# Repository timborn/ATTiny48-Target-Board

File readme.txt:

Fri Jun 16 17:11:15 MST 2023
----------------------------
_X_ add pads for ISP connector
_X_ gotta have an LED to we can detect life
_X_ decoupling caps between VCC and GND
_na pull-up resistor on VCC
    Data sheet section 22, Electrical Characteristics shows the reset pin
    has a built-in pull-up resistor of between 30 and 60 Ohms, so we shouldn't 
    need an external pull-up, especially for a bare bones system.
_X_ noise filtering ckt between VCC and AVCC (so ADC works better)
_X_ pin headers to fit std breadboard
_X_ reset button
_X_ panelize boards
_X_ fix installation of kikit that broke with upgrade of KiCad to 7.0.5
___ UNpanelize board

1.  Git Tag each version and make sure you push tags to origin
    https://git-scm.com/book/en/v2/Git-Basics-Tagging
2.  When I went to PCBWAY to place the order, I had panelized 2x4 which ended up
    being 110.5 x 104.7mm.  The price for the boards was $35.  
    When I dropped the size to fit inside 100x100mm the price dropped to $5.
3.  When generating the Gerber files I got a stern warning:
    "Global solder mask minimum width and/or margin are not set to 0.
    Most board manufacturers expect 0 and use their own constraints for
    solder mask minimum width."

    File / Board Setup / Board Stackup / Solder Mask/Paste
    set 'Solder mask expansion' to 0
    set 'Solder mask minimum web width' to 0

    I compared my settings to the requirements from PCBWAY:
    https://www.pcbway.com/pcb_prototype/Pinted_Circuit_Board_Prototype.html
    I didn't find anything about solder mask web width, so I set it at zero
    per KiCad recommendation.  I did change minimum clearance between traces
    to 3mil (0.076mm) per PCBWAY recommendation.  These changes went in post v1.0.

4.  Found a forked trace on pin 22 GND.  Cleaned that up.
5.  Having difficulty with paneling.  Crashes often, and rarely allows me to iterate
    without having to start over with a clean project.  I picked off the command
    line that it builds (uses kikit) but it throws some error when I run it from 
    the command line.  I think I could iterate faster over panels if I had
    the command line stuff working.
6.  ... to that end, I upgraded from KiCad 7.02 to 7.0.5.  I think kikit maybe brew.
    When I installed 7.0.5 over 7.0.2 it went through the motions, but silently failed.
    I had to move the old KiCad folder out of /Applications for installation to complete.
7.  After upgrading to KiCad 7.0.5 it complained about KiKit and sent me here to install it:
    https://github.com/yaqwsx/KiKit/blob/master/doc/installation.md

    Before:
    R2D2:ATTiny48-Target-Board timborn$ kikit --version
    python -m kikit.ui, version 1.3.0

    NB KiCad installed it's own version of Python and kikit, so when I queried pip3
    to see what's up with KiKit, the default version in my PATH didn't know anything
    (which is weird, since I am able to invoke kikit).

    Using the "other" version of Python & friends from KiCad:
    R2D2:test timborn$ /Applications/KiCad/KiCad.app/Contents/Frameworks/Python.framework/Versions/Current/bin/pip3 show kikit

    As I already had the certificate in place ...
    $ curl -O https://raw.githubusercontent.com/yaqwsx/KiKit/master/scripts/installMacOS.bash
    $ sudo bash installMacOS.bash
    
    OK, that got kikit installed (turned out to be the same version).  I just needed to 
    go into KiCad Tools / Plugin and Content Manager and (re-)install kikit.

8. Apparently I have kikit running inside Docker:
   R2D2:test timborn$ docker run  yaqwsx/kikit --version
   I wonder how to use this for panelization.

   $ docker run yaqwsx/kikit panelize     --layout 'hspace: 2mm; vspace: 2mm; cols: 3'\
   --framing 'type: frame' \
   /Volumes/BlueMountain/Users/timborn/kikad/ATTiny48-Target-Board/ATTiny48-Target-Board.kicad_pcb panel.kicad_pcb
   An error occurred: Unable to open /Volumes/BlueMountain/Users/timborn/kikad/ATTiny48-Target-Board/ATTiny48-Target-Board.kicad_pcb for reading.
   No output files produced

   Using bind mount helped!
   # using a bind mount for a local directory so I can pass in the PCB to be panelized
   # and get the results back (the directory on the host in this case is $PWD).
   docker run --mount type=bind,source="$(pwd)",destination=/app yaqwsx/kikit panelize     \
   --layout 'hspace: 2mm; vspace: 2mm; cols: 3'     \
   --framing 'type: frame'     \
   /app/ATTiny48-Target-Board.kicad_pcb \
   /app/panel.kicad_pcb

   KiCad was unable to open this file because it was created with a 
   more recent version than the one you are running.

   Looks like I have to figure out how to update KiCad inside this container.

   OK, I have a clone of yaqwsx/KiKit here:
   /Volumes/BlueMountain/Users/timborn/kikad/KiKit
   In my notes there I see a one-line change to Dockerfile to update to KiCad 7.0:
  
   # ARG KICAD_VERSION="6.0"
   ARG KICAD_VERSION="7.0"

   Build an image called kikit (NOT yaqwsx/kikit):
   Docker build -t kikit .

   Update script.sh to use the correct docker image and Bob's Your Uncle™️

9. 5-8 can be summed up as 1) I upgraded versions of KiCad and KiKit and 
   2) running kikit for paneling inside a Docker container is *way* more
   stable and faster for iterating until you get something you like.

10. When I submitted my 1x3 panelized version (well inside the 100x100mm) they
   changed the price from $5 to $33.  $15 for USPS, so $20/5 boards vs $48/15 boards.

11. TODO: add a four pin header for FTDI so I can have USB to serial interface.
   Is there a standard for this interface?  Seems like the order of pins is all over the place.

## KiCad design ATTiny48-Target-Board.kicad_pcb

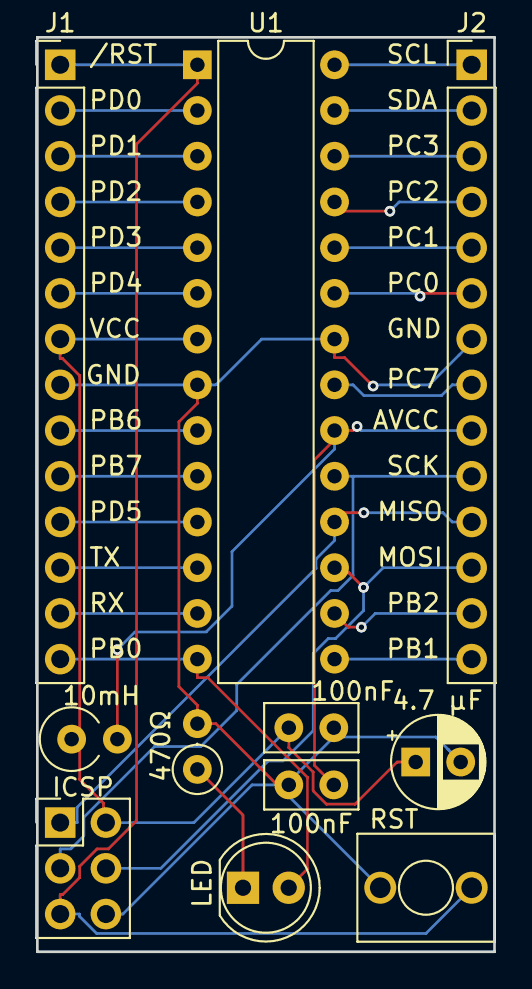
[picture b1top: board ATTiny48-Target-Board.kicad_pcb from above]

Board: 2 copper layers, 25.4 x 50.8 mm, 11 parts (0 on the bottom side), 28 nets.

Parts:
4.7 µF: 4.7 uF; CP_Radial_D5.0mm_P2.50mm
10mH: 10 mH; L_Axial_L7.0mm_D3.3mm_P2.54mm_Vertical_Fastron_MICC
100nF, 100nF#2: 100 nF; C_Disc_D5.0mm_W2.5mm_P2.50mm
470Ω: 470; R_Axial_DIN0207_L6.3mm_D2.5mm_P2.54mm_Vertical
ICSP: AVR-ISP-6; PinHeader_2x03_P2.54mm_Vertical
J1, J2: Conn_01x14_Pin; PinHeader_1x14_P2.54mm_Vertical
LED: LED; LED_D5.0mm
RST: SW_Push; TDB_Tayda_Tactile_SPST
U1: ATtiny48-P; DIP-28_W7.62mm

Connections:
AVCC: 10mH.2, 100nF.2, J2.9, U1.20 (AVCC)
GND: 4.7 µF.2, 100nF.1, 100nF#2.2, 470Ω.2, ICSP.6 (GND), J1.8, J2.7, RST.1, U1.8 (GND), U1.22 (GND)
unnamed: 470Ω.1, LED.1 (K)
PB0: J1.14, LED.2 (A), U1.14 (PB0)
PB1: J2.14, U1.15 (PB1)
PB2: J2.13, U1.16 (PB2)
PB3: ICSP.4 (MOSI), J2.12, U1.17 (PB3)
PB4: ICSP.1 (MISO), J2.11, U1.18 (PB4)
PB5: ICSP.3 (SCK), J2.10, U1.19 (PB5)
PB6: J1.9, U1.9 (PB6)
PB7: J1.10, U1.10 (PB7)
PC0: J2.6, U1.23 (PC0)
PC1: J2.5, U1.24 (PC1)
PC2: J2.4, U1.25 (PC2)
PC3: J2.3, U1.26 (PC3)
PC4: J2.2, U1.27 (PC4)
PC5: J2.1, U1.28 (PC5)
PC7: J2.8, U1.21 (PC7)
PD0: J1.2, U1.2 (PD0)
PD1: J1.3, U1.3 (PD1)
PD2: J1.4, U1.4 (PD2)
PD3: J1.5, U1.5 (PD3)
PD4: J1.6, U1.6 (PD4)
PD5: J1.11, U1.11 (PD5)
PD6: J1.12, U1.12 (PD6)
PD7: J1.13, U1.13 (PD7)
RESET: ICSP.5 (~RST), J1.1, RST.2, U1.1 (~RESET/PC6)
VCC: 4.7 µF.1, 10mH.1, 100nF#2.1, ICSP.2 (VCC), J1.7, U1.7 (VCC)

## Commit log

2023-06-13 Made a compact 25.4 x 50.8mm board with space for ATtiny44/48, a reset button, an LED, ICSP connector, and proper noise decoupling between VCC and AVCC. A decent start on a useful bit of common boile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
    Not included:
    1. external crystal. The internal one is fine until it's not.
    So far I haven't found the need.
    2. USB connector. Once I figure out how to add serial I/O and program
    over the USB connector (preferably USB-C) I will add it, but I don't
    know how. Yet.
2023-06-13 v1.0 ready to be paneled and sent to fab
2023-06-14 v1.0 before I panelize it
2023-06-14 v1.1 change hinky trace on pin 22
2023-06-14 gerbers after panelizing
2023-06-14 add script for panelizing
2023-06-14 v1.1 this is the version sent to PCBWAY using gerbers.zip and panel-script.sh
2023-06-14 moved gerbers.zip to panel-gerbers.zip to make room for gerber files for single boards
2023-06-14 Still v1.1, but I dropped the panels. This is the version sent to PCBWAY (again). mv gerbers.zip to panel-gerbers.zip generate gerber.zip from UNpaneled version
2023-06-14 v1.2 sent to PCBWAY
2023-06-14 somehow I managed to zip up v1.1 and caught it at gerber preview at PCBWAY. This should be gerber files for v1.2
2023-06-17 added 3D of version 1.2 of the BBMC
2023-06-17 next version add pin header for USB serial interface
